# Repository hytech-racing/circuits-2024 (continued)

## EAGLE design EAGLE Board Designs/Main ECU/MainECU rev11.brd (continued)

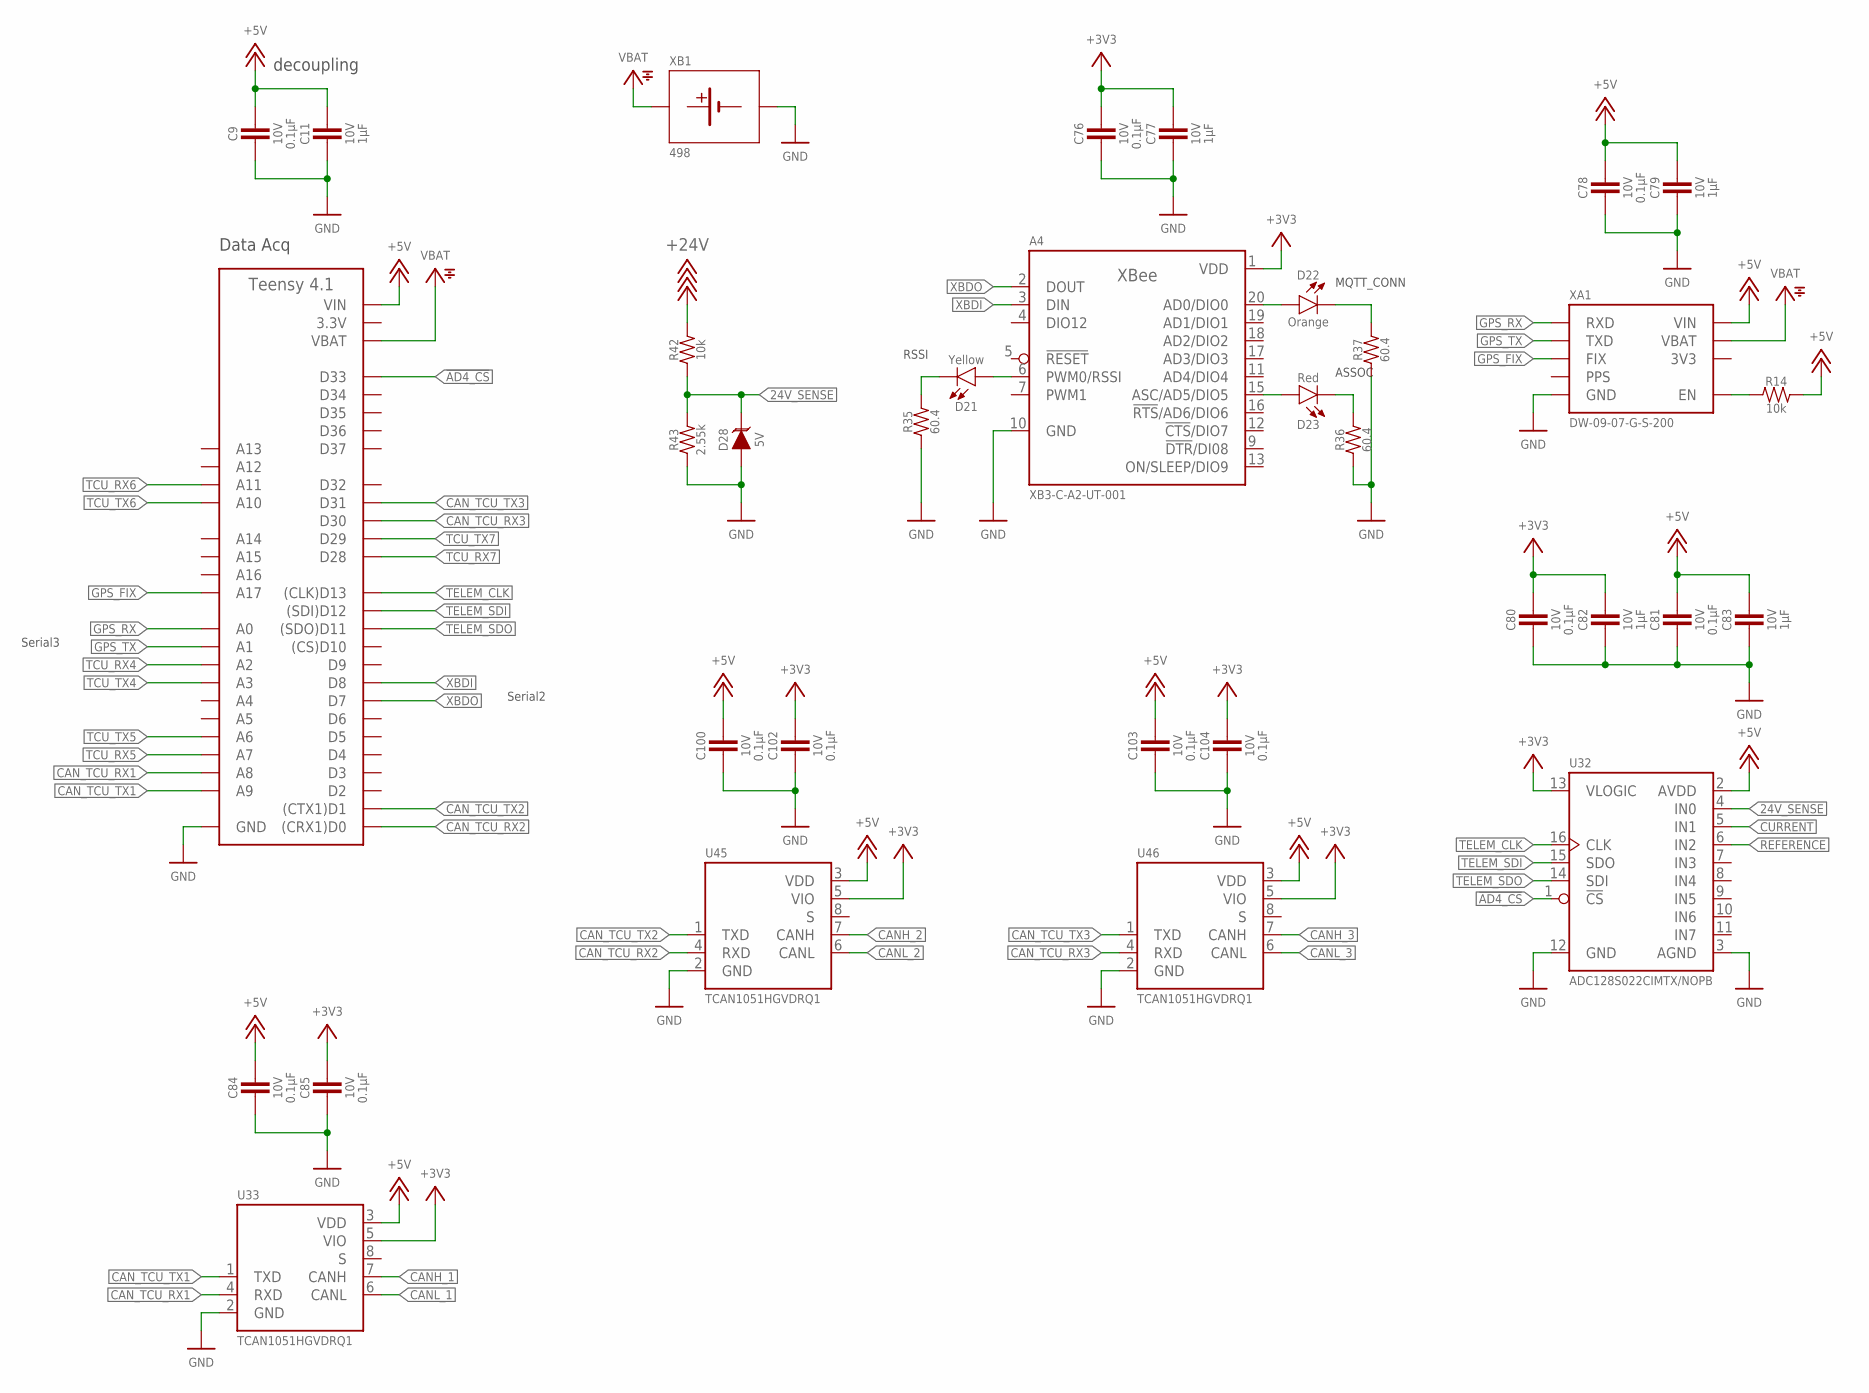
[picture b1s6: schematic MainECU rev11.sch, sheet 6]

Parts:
A3: TEENSY_4.1; TEENSY_LONG_EXT
A4: XB3-C-A2-UT-001; XBEE
C9, C76, C78, C80, C81, C84, C85, C100, C102, C103, C104: CAPACITOR_0603_10V_0.1UF; 0603-CAP
C11, C77, C79, C82, C83: CAPACITOR_0603_10V_1UF; 0603-CAP
D21: LED_0603_YELLOW; 0603-LED
D22: LED_0603_ORANGE; 0603-LED
D23: LED_0603_RED; 0603-LED
D28: TVS_5V; SOT-23
R14, R42: RESISTOR_0603_10K; 0603-RES
R35, R36, R37: RESISTOR_0603_60.4; 0603-RES
R43: RESISTOR_0603_2.55K; 0603-RES
U32: ADC128S022; TSSOP-16
U33, U45, U46: TCAN1051HQV-Q1; SOIC-08(NARROW,0.15")
XA1: ULTIMATE_GPS
XB1: BATTERY_HOLDER_KEYSTONE_498; 498

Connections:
3.3V: A3.3V3 (3.3V), A3.3V3@2 (3.3V), A3.3V3@3 (3.3V); also elsewhere on the board
3V3: XA1.3.3V (3V3)
24V_SENSE: D28.3 (C), R42.1, R43.2, U32.4 (IN0)
!AD4_CS: A3.D33, U32.1 (!CS!)
+3V3: A4.1 (VDD), C76.1, C77.1, C80.1, C82.1, C85.1, C102.1, C104.1, U32.13 (VLOGIC), U33.5 (VIO), U45.5 (VIO), U46.5 (VIO); also elsewhere on the board
+5V: A3.VIN, C9.1, C11.1, C78.1, C79.1, C81.1, C83.1, C84.1, C100.1, C103.1, R14.2, U32.2 (AVDD), U33.3 (VDD), U45.3 (VDD), U46.3 (VDD), XA1.VIN; also elsewhere on the board
+24V: R42.2; also elsewhere on the board
CANH_1: U33.7 (CANH); also elsewhere on the board
CANH_2: U45.7 (CANH); also elsewhere on the board
CANH_3: U46.7 (CANH); also elsewhere on the board
CANL_1: U33.6 (CANL); also elsewhere on the board
CANL_2: U45.6 (CANL); also elsewhere on the board
CANL_3: U46.6 (CANL); also elsewhere on the board
CAN_TCU_RX1: A3.D22 (A8), U33.4 (RXD)
CAN_TCU_RX2: A3.D0 ((CRX1)D0), U45.4 (RXD)
CAN_TCU_RX3: A3.D30, U46.4 (RXD)
CAN_TCU_TX1: A3.D23 (A9), U33.1 (TXD)
CAN_TCU_TX2: A3.D1 ((CTX1)D1), U45.1 (TXD)
CAN_TCU_TX3: A3.D31, U46.1 (TXD)
CURRENT: U32.5 (IN1); also elsewhere on the board
GND: A3.AGND/GND (GND), A3.GND, A3.GND@2 (GND), A4.10 (GND), C9.2, C11.2, C76.2, C77.2, C78.2, C79.2, C80.2, C81.2, C82.2, C83.2, C84.2, C85.2, C100.2, C102.2, C103.2, C104.2, D28.1 (A), R35.1, R36.1, R37.1, R43.1, U32.3 (AGND), U32.12 (GND), U33.2 (GND), U45.2 (GND), U46.2 (GND), XA1.GND, XB1.2 (MINUS); also elsewhere on the board
GPS_FIX: A3.D41 (A17), XA1.FIX
GPS_RX: A3.D14 (A0), XA1.RX (RXD)
GPS_TX: A3.D15 (A1), XA1.TX (TXD)
unnamed: D21.1 (C), R35.2
unnamed: A4.6 (PWM0/RSSI), D21.2 (A)
unnamed: A4.20 (AD0/DIO0), D22.2 (A)
unnamed: A4.15 (ASC/AD5/DIO5), D23.2 (A)
unnamed: R14.1, XA1.EN
unnamed: D22.1 (C), R37.2
unnamed: D23.1 (C), R36.2
REFERENCE: U32.6 (IN2); also elsewhere on the board
TCU_RX4: A3.D16 (A2); also elsewhere on the board
TCU_RX5: A3.D21 (A7); also elsewhere on the board
TCU_RX6: A3.D25 (A11); also elsewhere on the board
TCU_RX7: A3.D28; also elsewhere on the board
TCU_TX4: A3.D17 (A3); also elsewhere on the board
TCU_TX5: A3.D20 (A6); also elsewhere on the board
TCU_TX6: A3.D24 (A10); also elsewhere on the board
TCU_TX7: A3.D29; also elsewhere on the board
TELEM_CLK: A3.D13 ((CLK)D13), U32.16 (CLK)
TELEM_SDI: A3.D12 ((SDI)D12), U32.15 (SDO)
TELEM_SDO: A3.D11 ((SDO)D11), U32.14 (SDI)
VBAT: A3.VBAT, XA1.VBAT, XB1.1 (PLUS); also elsewhere on the board
XBDI: A3.D8, A4.3 (DIN)
XBDO: A3.D7, A4.2 (DOUT)

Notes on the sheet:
decoupling
Data Acq
Serial2
MQTT_CONN
ASSOC
RSSI
Serial3

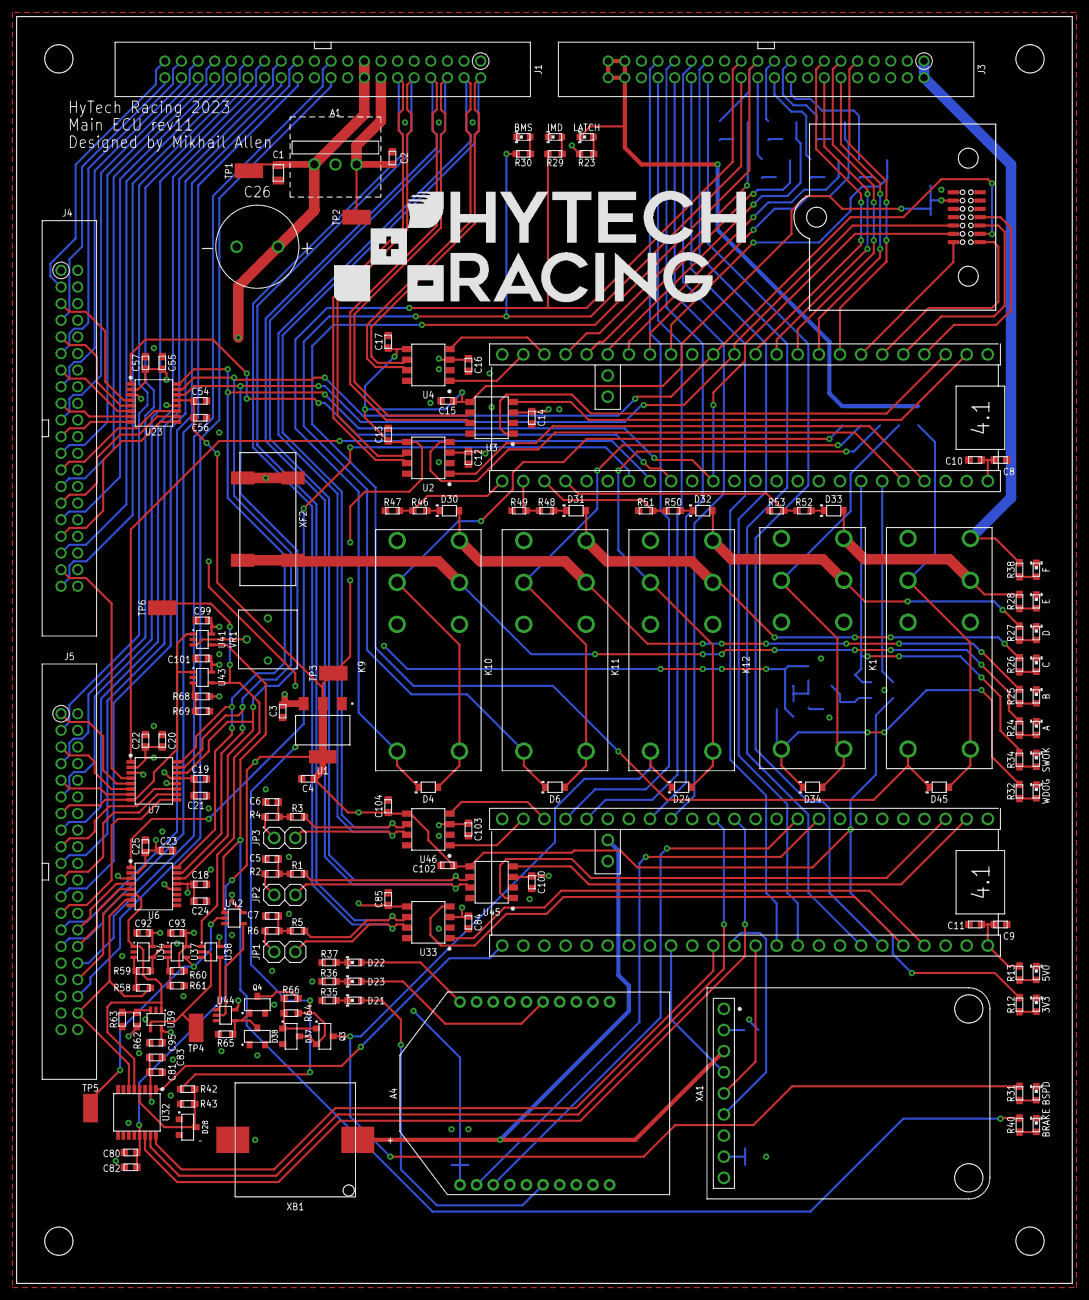
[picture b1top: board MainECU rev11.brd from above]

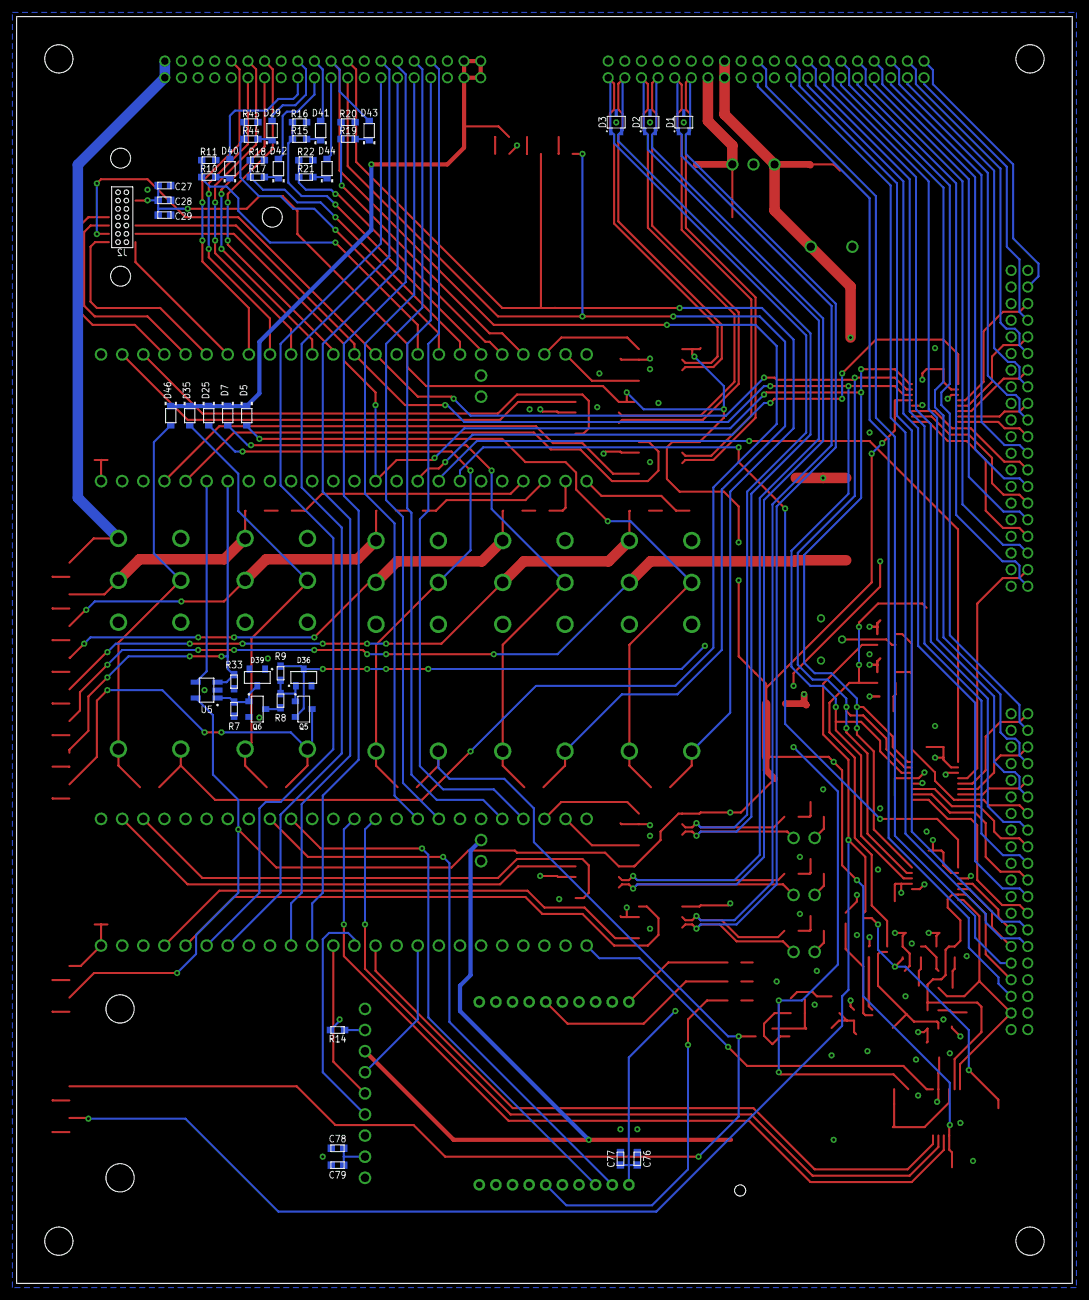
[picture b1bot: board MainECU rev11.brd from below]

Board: 4 copper layers, 127.0 x 152.4 mm, 216 parts (43 on the bottom side), 187 nets.

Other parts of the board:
U$5: LOGO_HYTECH_LARGE
U$9, U$10, U$11, U$12: MOUNTING_M3

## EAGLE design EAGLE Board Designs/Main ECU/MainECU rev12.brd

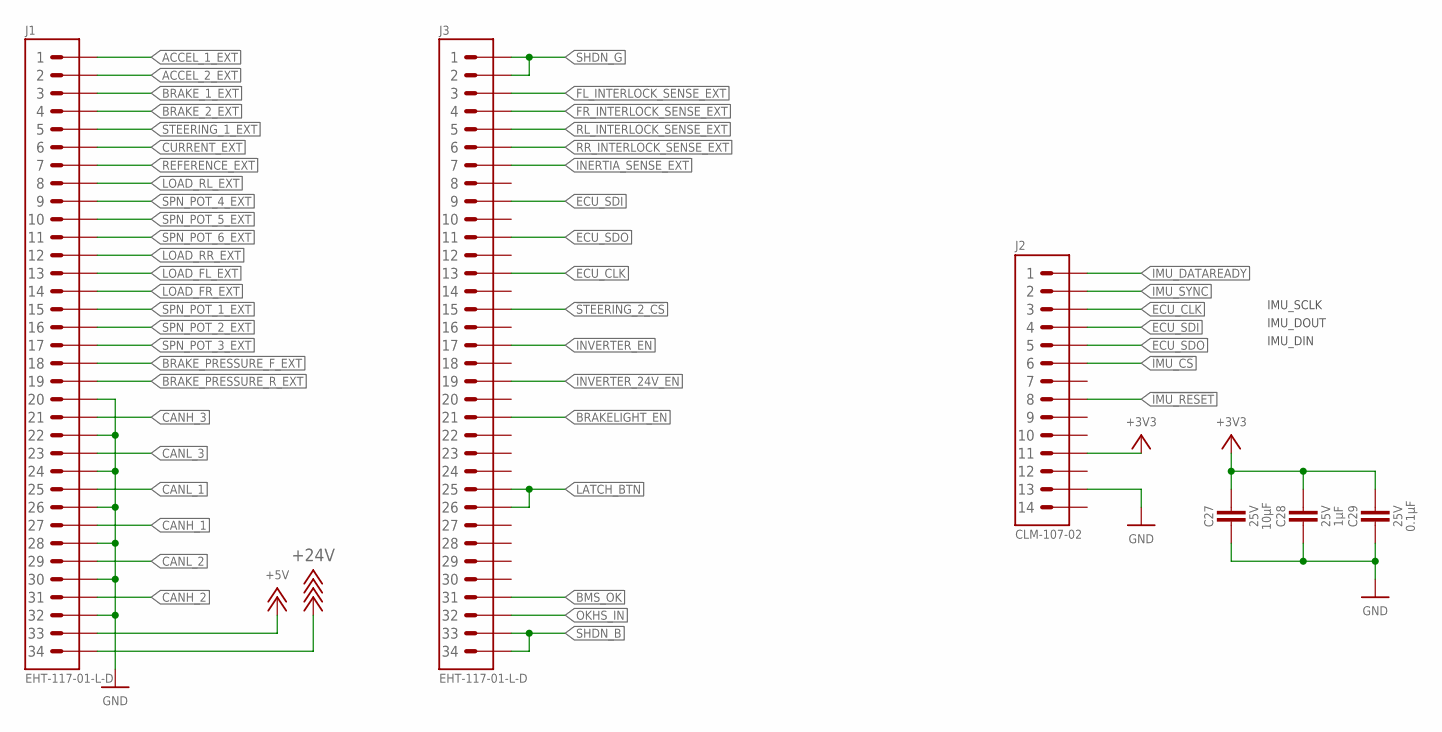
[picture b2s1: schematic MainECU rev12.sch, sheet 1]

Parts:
C27: CAPACITOR_0603_25V_10UF; 0603-CAP
C28: CAPACITOR_0603_25V_1UF; 0603-CAP
C29: CAPACITOR_0603_25V_0.1UF; 0603-CAP
J1, J3: CONNECTOR-34__; EHT-117-01
J2: ADIS16460

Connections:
!IMU_CS: J2.6; also elsewhere on the board
!IMU_RESET: J2.8; also elsewhere on the board
!STEERING_2_CS: J3.15; also elsewhere on the board
+3V3: C27.1, C28.1, C29.1, J2.11; also elsewhere on the board
+5V: J1.33; also elsewhere on the board
+24V: J1.34; also elsewhere on the board
ACCEL_1_EXT: J1.1; also elsewhere on the board
ACCEL_2_EXT: J1.2; also elsewhere on the board
BMS_OK: J3.31; also elsewhere on the board
BRAKELIGHT_EN: J3.21; also elsewhere on the board
BRAKE_1_EXT: J1.3; also elsewhere on the board
BRAKE_2_EXT: J1.4; also elsewhere on the board
BRAKE_PRESSURE_F_EXT: J1.18; also elsewhere on the board
BRAKE_PRESSURE_R_EXT: J1.19; also elsewhere on the board
CANH_1: J1.27; also elsewhere on the board
CANH_2: J1.31; also elsewhere on the board
CANH_3: J1.21; also elsewhere on the board
CANL_1: J1.25; also elsewhere on the board
CANL_2: J1.29; also elsewhere on the board
CANL_3: J1.23; also elsewhere on the board
CURRENT_EXT: J1.6; also elsewhere on the board
ECU_CLK: J2.3, J3.13; also elsewhere on the board
ECU_SDI: J2.4, J3.9; also elsewhere on the board
ECU_SDO: J2.5, J3.11; also elsewhere on the board
FL_INTERLOCK_SENSE_EXT: J3.3; also elsewhere on the board
FR_INTERLOCK_SENSE_EXT: J3.4; also elsewhere on the board
GND: C27.2, C28.2, C29.2, J1.20, J1.22, J1.24, J1.26, J1.28, J1.30, J1.32, J2.13; also elsewhere on the board
IMU_DATAREADY: J2.1; also elsewhere on the board
IMU_SYNC: J2.2; also elsewhere on the board
INERTIA_SENSE_EXT: J3.7; also elsewhere on the board
INVERTER_24V_EN: J3.19; also elsewhere on the board
INVERTER_EN: J3.17; also elsewhere on the board
LATCH_BTN: J3.25, J3.26; also elsewhere on the board
LOAD_FL_EXT: J1.13; also elsewhere on the board
LOAD_FR_EXT: J1.14; also elsewhere on the board
LOAD_RL_EXT: J1.8; also elsewhere on the board
LOAD_RR_EXT: J1.12; also elsewhere on the board
OKHS_IN: J3.32; also elsewhere on the board
REFERENCE_EXT: J1.7; also elsewhere on the board
RL_INTERLOCK_SENSE_EXT: J3.5; also elsewhere on the board
RR_INTERLOCK_SENSE_EXT: J3.6; also elsewhere on the board
SHDN_B: J3.33, J3.34; also elsewhere on the board
SHDN_G: J3.1, J3.2; also elsewhere on the board
SPN_POT_1_EXT: J1.15; also elsewhere on the board
SPN_POT_2_EXT: J1.16; also elsewhere on the board
SPN_POT_3_EXT: J1.17; also elsewhere on the board
SPN_POT_4_EXT: J1.9; also elsewhere on the board
SPN_POT_5_EXT: J1.10; also elsewhere on the board
SPN_POT_6_EXT: J1.11; also elsewhere on the board
STEERING_1_EXT: J1.5; also elsewhere on the board

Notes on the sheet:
IMU_DOUT
IMU_SCLK
IMU_DIN

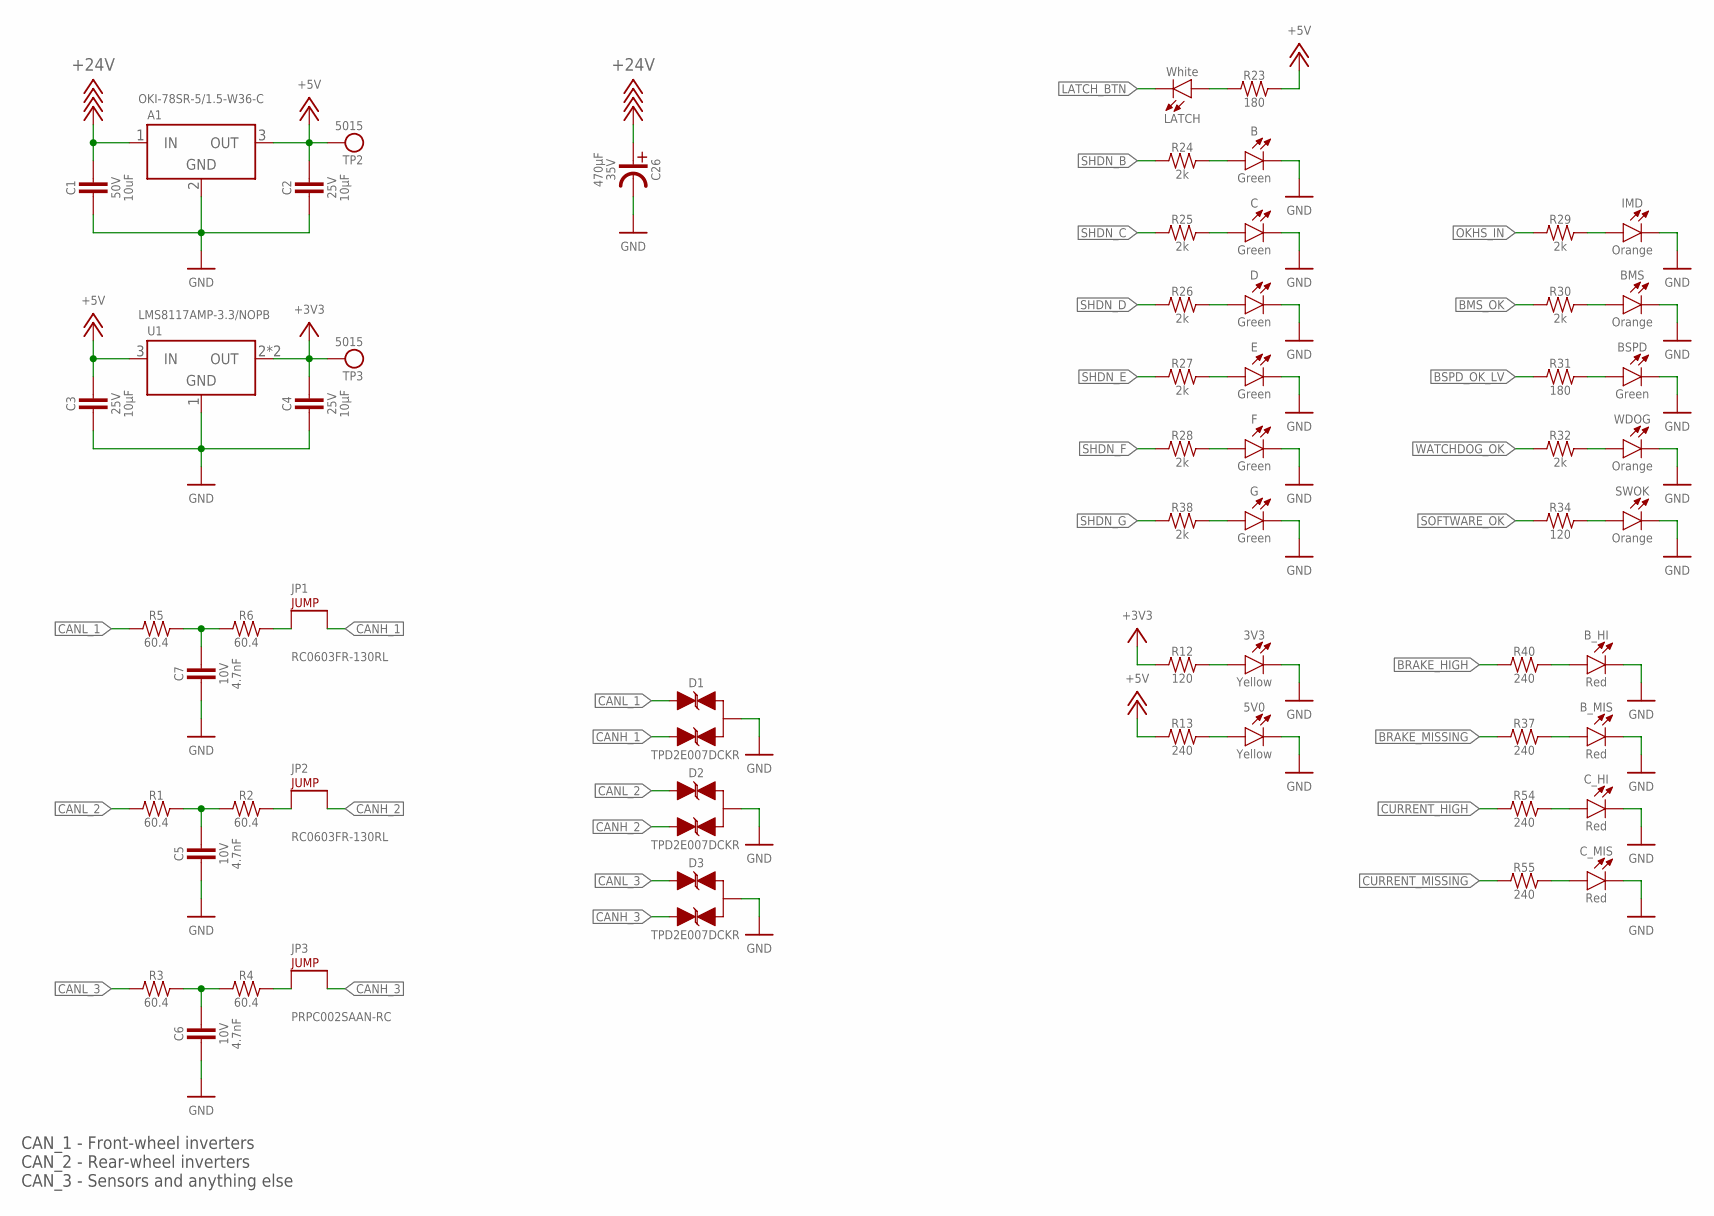
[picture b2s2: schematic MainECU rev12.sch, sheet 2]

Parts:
3V3, 5V0: LED_0603_YELLOW; 0603-LED
A1: VOLTAGE_REGULATOR_MODULE_OKI-78SR_5V; OKI-78SR
B: LED_0603_GREEN; 0603-LED
BMS: LED_0603_ORANGE; 0603-LED
BSPD: LED_0603_GREEN; 0603-LED
B_HI: LED_0603_RED; 0603-LED
B_MIS: LED_0603_RED; 0603-LED
C: LED_0603_GREEN; 0603-LED
C1: CAPACITOR_0805_50V_10UF; 0805-CAP
C2, C3, C4: CAPACITOR_0603_25V_10UF; 0603-CAP
C5, C6, C7: CAPACITOR_0603_10V_4.7NF; 0603-CAP
C26: EEH-AZS1V471B; EEH-AZS
C_HI: LED_0603_RED; 0603-LED
C_MIS: LED_0603_RED; 0603-LED
D: LED_0603_GREEN; 0603-LED
D1, D2, D3: TVS_BIDIRECTIONAL_DUAL; SC-70-3
E: LED_0603_GREEN; 0603-LED
F: LED_0603_GREEN; 0603-LED
G: LED_0603_GREEN; 0603-LED
IMD: LED_0603_ORANGE; 0603-LED
JP1, JP2: JUMPER_0603_; 0603-RES
JP3: JUMPER__1X02; 1X02
LATCH: LED_0603_WHITE; 0603-LED
R1, R2, R3, R4, R5, R6: RESISTOR_0603_60.4; 0603-RES
R12, R34: RESISTOR_0603_120; 0603-RES
R13, R37, R40, R54, R55: RESISTOR_0603_240; 0603-RES
R23, R31: RESISTOR_0603_180; 0603-RES
R24, R25, R26, R27, R28, R29, R30, R32, R38: RESISTOR_0603_2K; 0603-RES
SWOK: LED_0603_ORANGE; 0603-LED
TP2, TP3: TEST_POINT; 5015
U1: VOLTAGE_REGULATOR_SOT-223_3.3V; SOT-223
WDOG: LED_0603_ORANGE; 0603-LED

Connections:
+3V3: C4.1, R12.1, TP3.1, U1.2 (OUT), U1.4 (OUT); also elsewhere on the board
+5V: A1.3 (OUT), C2.1, C3.1, R13.1, R23.2, TP2.1, U1.3 (IN); also elsewhere on the board
+24V: A1.1 (IN), C1.1, C26.PLUS; also elsewhere on the board
BMS_OK: R30.1; also elsewhere on the board
BRAKE_HIGH: R40.1; also elsewhere on the board
BRAKE_MISSING: R37.1; also elsewhere on the board
BSPD_OK_LV: R31.1; also elsewhere on the board
CANH_1: D1.2 (C2), JP1.2; also elsewhere on the board
CANH_2: D2.2 (C2), JP2.2; also elsewhere on the board
CANH_3: D3.2 (C2), JP3.2; also elsewhere on the board
CANL_1: D1.1 (C1), R5.1; also elsewhere on the board
CANL_2: D2.1 (C1), R1.1; also elsewhere on the board
CANL_3: D3.1 (C1), R3.1; also elsewhere on the board
CURRENT_HIGH: R54.1; also elsewhere on the board
CURRENT_MISSING: R55.1; also elsewhere on the board
GND: 3V3.1 (C), 5V0.1 (C), A1.2 (GND), B.1 (C), BMS.1 (C), BSPD.1 (C), B_HI.1 (C), B_MIS.1 (C), C.1 (C), C1.2, C2.2, C3.2, C4.2, C5.2, C6.2, C7.2, C26.MINUS, C_HI.1 (C), C_MIS.1 (C), D.1 (C), D1.3 (A), D2.3 (A), D3.3 (A), E.1 (C), F.1 (C), G.1 (C), IMD.1 (C), SWOK.1 (C), U1.1 (GND), WDOG.1 (C); also elsewhere on the board
LATCH_BTN: LATCH.1 (C); also elsewhere on the board
unnamed: JP1.1, R6.2
unnamed: JP2.1, R2.2
unnamed: JP3.1, R4.2
unnamed: C5.1, R1.2, R2.1
unnamed: C6.1, R3.2, R4.1
unnamed: C7.1, R5.2, R6.1
unnamed: G.2 (A), R38.2
unnamed: LATCH.2 (A), R23.1
unnamed: B.2 (A), R24.2
unnamed: C.2 (A), R25.2
unnamed: D.2 (A), R26.2
unnamed: E.2 (A), R27.2
unnamed: F.2 (A), R28.2
unnamed: B_MIS.2 (A), R37.2
unnamed: C_HI.2 (A), R54.2
unnamed: C_MIS.2 (A), R55.2
unnamed: IMD.2 (A), R29.2
unnamed: BMS.2 (A), R30.2
unnamed: BSPD.2 (A), R31.2
unnamed: R32.2, WDOG.2 (A)
unnamed: 3V3.2 (A), R12.2
unnamed: R34.2, SWOK.2 (A)
unnamed: 5V0.2 (A), R13.2
unnamed: B_HI.2 (A), R40.2
OKHS_IN: R29.1; also elsewhere on the board
SHDN_B: R24.1; also elsewhere on the board
SHDN_C: R25.1; also elsewhere on the board
SHDN_D: R26.1; also elsewhere on the board
SHDN_E: R27.1; also elsewhere on the board
SHDN_F: R28.1; also elsewhere on the board
SHDN_G: R38.1; also elsewhere on the board
SOFTWARE_OK: R34.1; also elsewhere on the board
WATCHDOG_OK: R32.1; also elsewhere on the board

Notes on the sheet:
CAN_1 - Front-wheel inverters CAN_2 - Rear-wheel inverters CAN_3 - Sensors and anything else

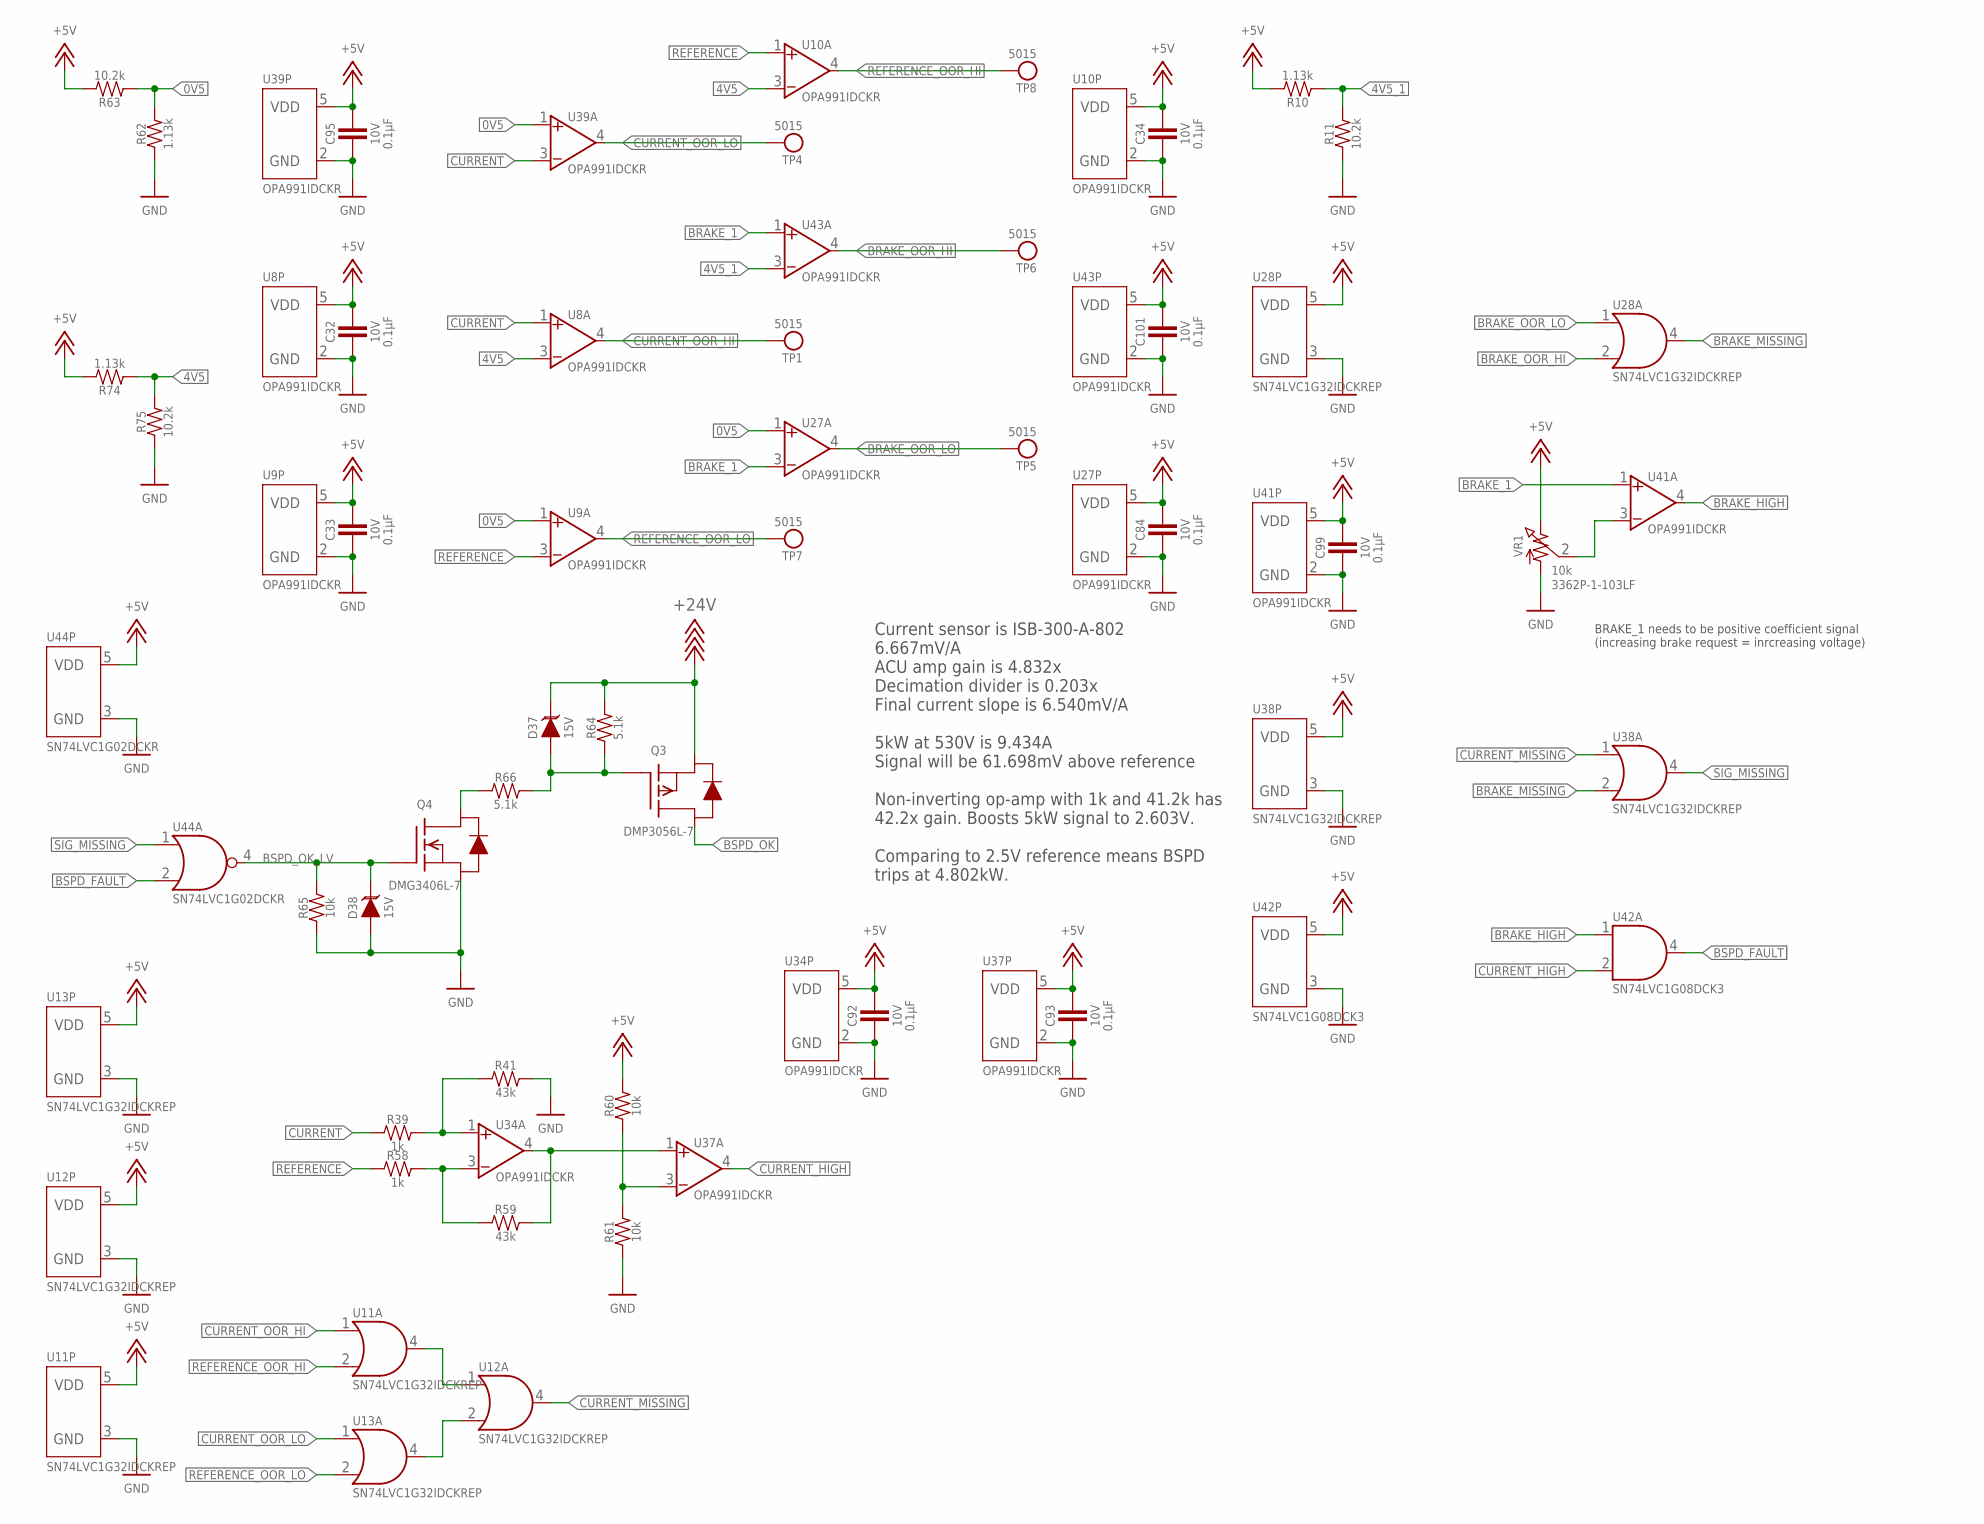
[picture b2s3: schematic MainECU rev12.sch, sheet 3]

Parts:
C32, C33, C34, C84, C92, C93, C95, C99, C101: CAPACITOR_0603_10V_0.1UF; 0603-CAP
D37, D38: TVS__15V; SOT-23
Q3: TRANSISTOR_P_MOS_SOT-23_DMP3056L-7; SOT-23
Q4: TRANSISTOR_N_MOS__DMG3406L-7; SOT-23
R10, R62, R74: RESISTOR_0603_1.13K; 0603-RES
R11, R63, R75: RESISTOR_0603_10.2K; 0603-RES
R39, R58: RESISTOR_0603_1K; 0603-RES
R41, R59: RESISTOR_0603_43K; 0603-RES
R60, R61, R65: RESISTOR_0603_10K; 0603-RES
R64, R66: RESISTOR_0603_5.1K; 0603-RES
TP1, TP4, TP5, TP6, TP7, TP8: TEST_POINT; 5015
U8, U9, U10, U27, U34, U37, U39, U41, U43: OPAMP_1_CHANNEL_OPA991; SC-70-5
U11, U12, U13, U28, U38: LOGICGATE_OR; SC-70-5
U42: LOGICGATE_AND_DCK3; SC-70-5
U44: LOGICGATE_NOR; SC-70-5
VR1: RESISTOR_TRIMPOT_10K_3362P; 3362P

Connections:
0V5: R62.2, R63.1, U9.1 (VIN+), U27.1 (VIN+), U39.1 (VIN+)
4V5: R74.1, R75.2, U8.3 (VIN-), U10.3 (VIN-)
4V5_1: R10.1, R11.2, U43.3 (VIN-)
+5V: C32.1, C33.1, C34.1, C84.1, C92.1, C93.1, C95.1, C99.1, C101.1, R10.2, R60.2, R63.2, R74.2, U8.5 (VDD), U9.5 (VDD), U10.5 (VDD), U11.5 (VDD), U12.5 (VDD), U13.5 (VDD), U27.5 (VDD), U28.5 (VDD), U34.5 (VDD), U37.5 (VDD), U38.5 (VDD), U39.5 (VDD), U41.5 (VDD), U42.5 (VDD), U43.5 (VDD), U44.5 (VDD), VR1.3 (2); also elsewhere on the board
+24V: D37.3 (C), Q3.2 (S), R64.2; also elsewhere on the board
BRAKE_1: U27.3 (VIN-), U41.1 (VIN+), U43.1 (VIN+); also elsewhere on the board
BRAKE_HIGH: U41.4 (VOUT), U42.1 (IN1); also elsewhere on the board
BRAKE_MISSING: U28.4 (OUT), U38.2 (IN2); also elsewhere on the board
BRAKE_OOR_HI: TP6.1, U28.2 (IN2), U43.4 (VOUT)
BRAKE_OOR_LO: TP5.1, U27.4 (VOUT), U28.1 (IN1)
BSPD_FAULT: U42.4 (OUT), U44.2 (IN2)
BSPD_OK: Q3.3 (D); also elsewhere on the board
BSPD_OK_LV: D38.3 (C), Q4.1 (G), R65.2, U44.4 (OUT); also elsewhere on the board
CURRENT: R39.1, U8.1 (VIN+), U39.3 (VIN-); also elsewhere on the board
CURRENT_HIGH: U37.4 (VOUT), U42.2 (IN2); also elsewhere on the board
CURRENT_MISSING: U12.4 (OUT), U38.1 (IN1); also elsewhere on the board
CURRENT_OOR_HI: TP1.1, U8.4 (VOUT), U11.1 (IN1)
CURRENT_OOR_LO: TP4.1, U13.1 (IN1), U39.4 (VOUT)
GND: C32.2, C33.2, C34.2, C84.2, C92.2, C93.2, C95.2, C99.2, C101.2, D38.1 (A), Q4.2 (S), R11.1, R41.2, R61.1, R62.1, R65.1, R75.1, U8.2 (GND), U9.2 (GND), U10.2 (GND), U11.3 (GND), U12.3 (GND), U13.3 (GND), U27.2 (GND), U28.3 (GND), U34.2 (GND), U37.2 (GND), U38.3 (GND), U39.2 (GND), U41.2 (GND), U42.3 (GND), U43.2 (GND), U44.3 (GND), VR1.1; also elsewhere on the board
unnamed: R39.2, R41.1, U34.1 (VIN+)
unnamed: R60.1, R61.2, U37.3 (VIN-)
unnamed: R58.2, R59.1, U34.3 (VIN-)
unnamed: R59.2, U34.4 (VOUT), U37.1 (VIN+)
unnamed: U41.3 (VIN-), VR1.2 (3)
unnamed: D37.1 (A), Q3.1 (G), R64.1, R66.2
unnamed: Q4.3 (D), R66.1
OOR_HI: U11.4 (OUT), U12.1 (IN1)
OOR_LO: U12.2 (IN2), U13.4 (OUT)
REFERENCE: R58.1, U9.3 (VIN-), U10.1 (VIN+); also elsewhere on the board
REFERENCE_OOR_HI: TP8.1, U10.4 (VOUT), U11.2 (IN2)
REFERENCE_OOR_LO: TP7.1, U9.4 (VOUT), U13.2 (IN2)
SIG_MISSING: U38.4 (OUT), U44.1 (IN1)

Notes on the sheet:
Current sensor is ISB-300-A-802 6.667mV/A ACU amp gain is 4.832x Decimation divider is 0.203x Final current slope is 6.540mV/A 5kW at 530V is 9.434A Signal will be 61.698mV above reference Non-inverting op-amp with 1k and 41.2k has 42.2x gain. Boosts 5kW signal to 2.603V. Comparing to 2.5V referenc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
BRAKE_1 needs to be positive coefficient signal (increasing brake request = inrcreasing voltage)
